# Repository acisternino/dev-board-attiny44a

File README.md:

# Development board for the ATtiny44A MCU

This is a simple board for experimenting with Microchip's ATtiny44A
8 bit microcontroller.

Main characteristics:

- Support for providing an external clock using a THT quartz.
- Decoupling of power pins.
- Correct termination of the /RESET pin.
- ICSP header.

A complete BOM is provided for [Digi-Key](https://www.digikey.com/).

## Feedback

This is my first PCB design. I'd love to receive feedback and ideas for
improvements from more experienced people.

PR's and Issues are welcome!

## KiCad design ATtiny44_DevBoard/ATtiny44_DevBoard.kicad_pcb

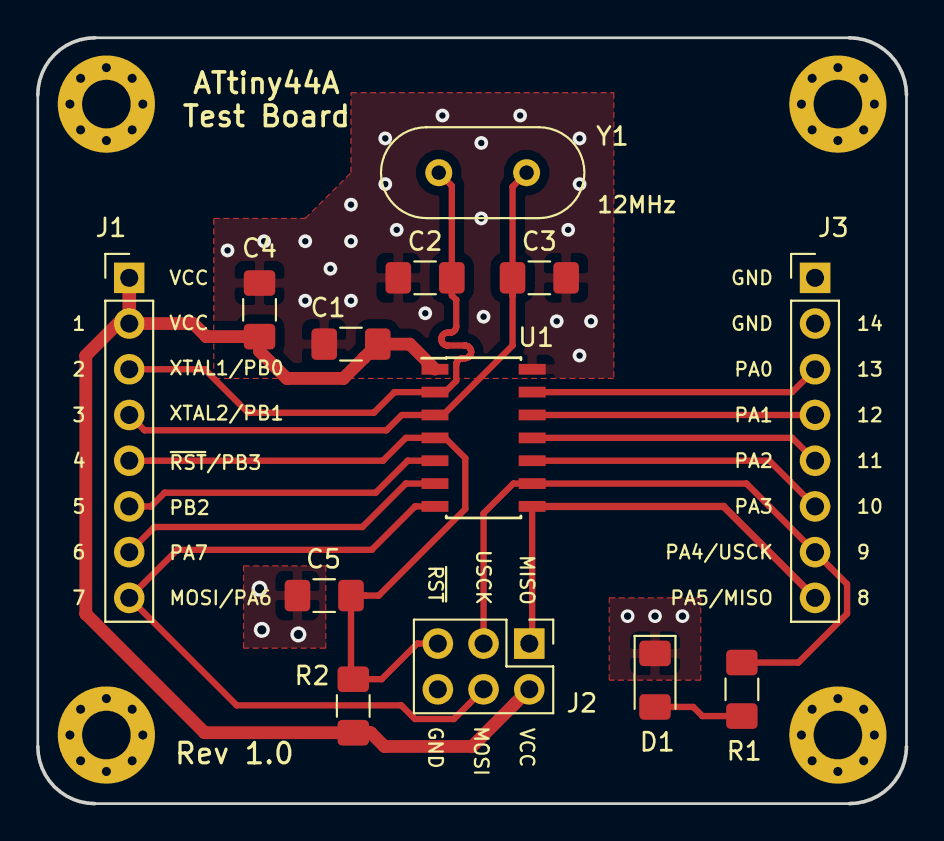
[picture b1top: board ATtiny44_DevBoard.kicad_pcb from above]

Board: 2 copper layers, 48.3 x 42.5 mm, 13 parts (0 on the bottom side), 15 nets.

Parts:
C1, C5: 0.1uF; C_1206_3216Metric_Pad1.42x1.75mm_HandSolder
C2, C3: 22pF; C_1206_3216Metric_Pad1.42x1.75mm_HandSolder
C4: 10uF; C_1206_3216Metric_Pad1.42x1.75mm_HandSolder
D1: LED; LED_1206_3216Metric_Pad1.42x1.75mm_HandSolder
J1, J3: Conn_01x08; PinHeader_1x08_P2.54mm_Vertical
J2: Conn_02x03_Odd_Even; PinHeader_2x03_P2.54mm_Vertical
R1: 1k; R_1206_3216Metric_Pad1.42x1.75mm_HandSolder
R2: 22k; R_1206_3216Metric_Pad1.42x1.75mm_HandSolder
U1: ATtiny44A-SSU; SOIC-14_3.9x8.7mm_P1.27mm
Y1: Crystal 12MHz; Crystal_HC49-U_Vertical

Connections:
/MISO: J2.1, J3.8, U1.8
/MOSI: J1.8, J2.4, U1.7
/PA0: J3.3, U1.13
/PA1: J3.4, U1.12
/PA2: J3.5, U1.11
/PA3: J3.6, U1.10
/PA7: J1.7, U1.6
/PB2: J1.6, U1.5
/USCK: J2.3, J3.7, R1.1, U1.9
/XTAL1: C2.1, J1.3, U1.2, Y1.1
/XTAL2: C3.1, J1.4, U1.3, Y1.2
/~RESET: C5.1, J1.5, J2.5, R2.2, U1.4
GND: C1.2, C2.2, C3.2, C4.2, C5.2, D1.1, J2.6, J3.1, J3.2, U1.14
unnamed: D1.2, R1.2
VCC: C1.1, C4.1, J1.1, J1.2, J2.2, R2.1, U1.1

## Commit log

2019-01-10 Fix typo in README
2019-01-10 Replace SMD quartz with simpler THT one
2019-01-10 Add renderings of the board
2019-01-10 Rename BOM file
2019-01-11 Update ATtiny44_DevBoard.kicad_pcb
    Connect mounting hole pads to GND
2019-01-11 Update gerbers and drill files
2019-01-15 Improvements after critique from Reddit
    - Made the traces larger: now signal is 16mils and Power is 30mils
    - Removed redundant trace to GND on the ISP header
    - Routed MOSI differently to avoid unnecessary trace on the bottom plane
2019-01-15 Move the crystal closer to the chip
2019-01-18 Improve decoupling capacitors placement
2019-01-21 Update pictures
2019-02-24 Update BOM
